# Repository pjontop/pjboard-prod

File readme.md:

# PJBOARD!!!

PJBoard is a low-profile, wireless split keyboard with 42 keys, two displays, and a very very thin case!

I made this because I wanted something that had the clean look of keyboards like the Geist Totem and the portability of the Voyager, but with a few more keys so it would be easier for me to actually learn how to use a split keyboard. Basically: how close can I get to the MacBook Pro of keyboards?

It uses Kailh Choc switches, two SuperMini nRF52840 controllers, nice!view displays, and ZMK firmware. Each half is completely wireless and has its own battery, power switch, and reset button.

## Features

- 42-key split layout: 3 rows of 6 keys and 3 thumb keys on each side
- Low-profile Kailh Choc switches
- Hotswap sockets, because desoldering an entire keyboard would not be very fun
- Fully wireless using two SuperMini nRF52840 controllers
- A nice!view display on each half for status info
- A super thin, rounded case with hidden screws
- Separate base, plate, and display-cover pieces for each half
- Power and reset switches built directly into both PCBs
- Three ZMK layers: Base, Lower, and Raise

## CAD Model

The case was made in Onshape. I started by importing the PCB outline and building everything around it, which sounds simple until Onshape decides one switch model needs approximately one billion triangles and takes four hours to import :sob:

The final case is made from three parts per side: the base, the switch plate, and the display cover. I wanted it to be really thin, rounded, and clean, so the mounting hardware is hidden and the top pieces sit flush with the case. There are also cutouts underneath the larger components so the case does not need to be unnecessarily chonky.

You can view and remix the original CAD here: **[PJBoard on Onshape](https://cad.onshape.com/documents/bca79db99613f7f3e83bd048/w/cf08fbd1a130c559ac00717d/e/9940d6e044f49ffd99b80cc9?renderMode=0&uiState=6a8a41c1502d0c8b6353df97)**

## PCB

Here is the PCB! It was designed in KiCad and it was definitely the largest rabbit hole in this entire project.

Each half uses a 4x6 key matrix with 21 populated positions, one diode per key, a SuperMini nRF52840, a nice!view header, an on/off switch, and a reset button. I moved the diodes into the centre control area to keep the switch area clean and used both copper layers to make the matrix routing actually possible.

The two halves are panelized together with breakaway tabs, so they can be manufactured as one PCB and snapped apart afterward. Fire, right?

## Firmware Overview

PJBoard runs [ZMK](https://zmk.dev/) since the keyboard is wireless. Prebuilt firmware for both halves is included in the [`firmware`](firmware/) folder, along with the source configuration.

The current keymap has three layers:

- **Base:** the normal QWERTY layout
- **Lower:** numbers, arrow keys, and Bluetooth controls
- **Raise:** symbols and brackets

The two thumb layer keys make it possible to keep the board at only 42 keys without losing all the useful stuff. The displays stay visible while the keyboard is awake and show the current keyboard status.

## BOM

Here should be the main stuff you need to build PJBoard:

A better BOM Can be found in the bom.csv in the main directory, this is merely meant for a rough look over.

- 42x Kailh Choc low-profile switches
- 42x Kailh Choc hotswap sockets
- 42x low-profile keycaps
- 42x SOD-123 diodes
- 2x SuperMini nRF52840 controllers
- 2x nice!view displays
- 2x small LiPo batteries
- 2x SMD power switches
- 2x SMD reset buttons
- 1x left/right PCB set
- 1x printed case set (left and right base, plate, and display cover)
- M2 hardware for mounting the PCBs and case parts

## Things I Learnt

This was my first time going this deep into designing a keyboard, and I learnt a TON.

- How keyboard matrices actually work instead of just vaguely knowing that diodes exist
- How to make and edit custom KiCad symbols and footprints
- How to route a two-layer split keyboard PCB without creating a heavenly amount of vias
- How to use multi-channel design tools instead of manually mirroring everything for 40 minutes
- How to bring a PCB outline into Onshape and design a case around the real dimensions
- How much the angle, stagger, and thumb position matter when designing for actual hands
- How ZMK separates boards, shields, keymaps, and configuration files (the naming absolutely did not help at first)
- That testing a layout before committing to the PCB saves a LOT of pain later

## Challenges I Faced

KiCad was the main villain here. I redesigned the PCB more than once, moved all the diodes around, fought with mirrored layouts, installed a plugin that did not even do what I needed, and eventually figured out a routing setup that was way cleaner. Sad reality: sometimes you really do just have to reroute the entire board.

The case also took a bunch of iteration. I wanted it thin, rounded, strong around the high-pressure keys, and completely clean from the top with no visible screws. Getting all of those things at once was much harder than sketching them, especially while keeping enough room for the hotswap sockets, batteries, controllers, and displays.

The firmware was another whole thing. ZMK is really powerful, but understanding boards vs shields, setting up both halves, fixing the matrix, and getting the displays working was WAY worse than I thought it would be. YouTube tutorials, random websites, and an unreasonable amount of debugging carried me through it.

Overall, though, I am super happy with how it turned out. I went from a rough idea and a hand sketch to a complete PCB, case, and working firmware setup. Very very fire.

## Thank You!

I am super thankful to [Hack Club](https://hackclub.com/) for funding this project and making it possible for me to actually build the weird keyboard I spent way too many hours obsessing over.

Also, Macondo is awesome. Seriously. Programs like this are the reason I can learn hardware by actually making something real instead of just watching another tutorial and forgetting everything five minutes later.

alr toodles :3

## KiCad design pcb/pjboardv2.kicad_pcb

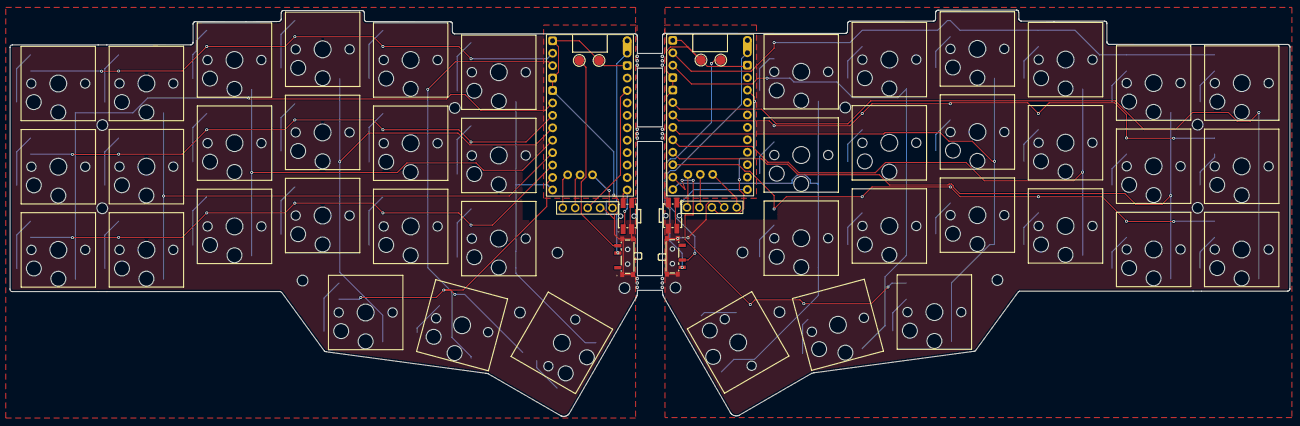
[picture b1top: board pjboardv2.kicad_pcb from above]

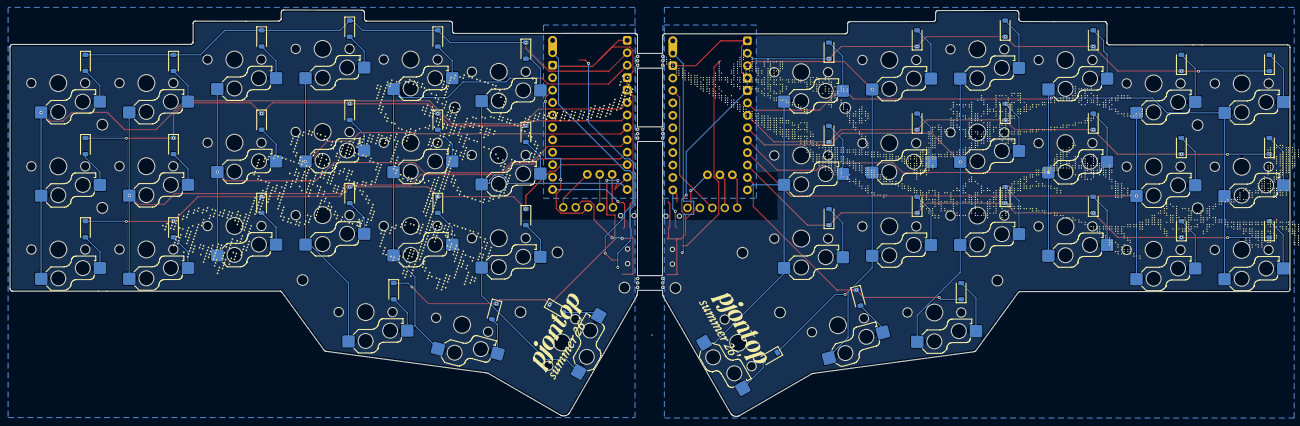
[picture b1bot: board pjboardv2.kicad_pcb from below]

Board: 2 copper layers, 261.5 x 83.0 mm, 113 parts (49 on the bottom side), 77 nets.

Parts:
D1, D2, D3, D4, D5, D6, D7, D8, D9, D10, D11, D12, D13, D14, D15, D16, D17, D18, D19, D20, D21, D22, D23, D24, D25, D26, D27, D28, D29, D30, D31, D32, D33, D34, D35, D36, D37, D38, D39, D40, D41, D42: D; D_SOD-123
Display3, Display4: nice!view; nice_view
H1, H2, H3: MountingHole; BreakawayTab
H4, H5, H6, H7, H8, H9, H10, H11, H12, H13, H14, H15, H16, H17: MountingHole; MountingHole_M2_NPTH
SW1, SW2, SW3, SW4, SW5, SW6, SW7, SW8, SW9, SW10, SW11, SW12, SW13, SW14, SW15, SW16, SW17, SW18, SW19, SW20, SW21, SW24, SW25, SW26, SW27, SW28, SW29, SW30, SW31, SW32, SW33, SW34, SW35, SW36, SW37, SW38, SW39, SW40, SW41, SW42, SW43, SW44: SW_Push; SW_Hotswap_Kailh_Choc_V1_Assembly
SW47, SW48: SSSS811101; SW-SMD_SSSS811101
SW49, SW50: TS-1114S-26; SW-SMD_4P-L4.7-W4.5-P1.70-LS6.4-EH
TP1, TP2, TP3, TP4: TestPoint; TestPoint_Pad_D2.0mm
U5, U6: SuperMini nRF52840; SuperMini_nRF52840_AH_USBup

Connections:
/left/COL0: SW1.1, SW2.1, SW3.1, U5.5 (P0.17)
/left/COL1: SW4.1, SW5.1, SW6.1, U5.9 (P1.00)
/left/COL2: SW7.1, SW8.1, SW9.1, U5.8 (P0.24)
/left/COL3: SW10.1, SW11.1, SW12.1, SW13.1, U5.7 (P0.22)
/left/COL4: SW14.1, SW15.1, SW16.1, SW17.1, U5.2 (P0.08)
/left/COL5: SW18.1, SW19.1, SW20.1, SW21.1, U5.12 (P1.06-LF)
/left/NVCC: Display3.3 (VCC), U5.16 (3V3)
/left/NVCS: Display3.5 (CS), U5.27 (P1.07-LF)
/left/NVMOSI: Display3.1 (MOSI), U5.25 (P1.01-LF)
/left/NVSCK: Display3.2 (SCK), U5.26 (P1.02-LF)
/left/ROW0: D1.1 (K), D4.1 (K), D7.1 (K), D10.1 (K), D14.1 (K), D18.1 (K), U5.1 (P0.06)
/left/ROW1: D2.1 (K), D5.1 (K), D8.1 (K), D11.1 (K), D15.1 (K), D19.1 (K), U5.6 (P0.20)
/left/ROW2: D3.1 (K), D6.1 (K), D9.1 (K), D12.1 (K), D16.1 (K), D20.1 (K), U5.10 (P0.11)
/left/ROW3: D13.1 (K), D17.1 (K), D21.1 (K), U5.11 (P1.04-LF)
/left/SRST: SW49.1, SW49.2, U5.24 (P0.09-LF)
/left/SWBAT+: SW47.2, U5.13 (BAT+), U5.29 (BAT+)
/right/COL0: SW24.1, SW25.1, SW26.1, U6.5 (P0.17)
/right/COL1: SW27.1, SW28.1, SW29.1, U6.9 (P1.00)
/right/COL2: SW30.1, SW31.1, SW32.1, U6.8 (P0.24)
/right/COL3: SW33.1, SW34.1, SW35.1, SW36.1, U6.7 (P0.22)
/right/COL4: SW37.1, SW38.1, SW39.1, SW40.1, U6.2 (P0.08)
/right/COL5: SW41.1, SW42.1, SW43.1, SW44.1, U6.12 (P1.06-LF)
/right/NVCC: Display4.3 (VCC), U6.16 (3V3)
/right/NVCS: Display4.5 (CS), U6.27 (P1.07-LF)
/right/NVMOSI: Display4.1 (MOSI), U6.25 (P1.01-LF)
/right/NVSCK: Display4.2 (SCK), U6.26 (P1.02-LF)
/right/ROW0: D22.1 (K), D25.1 (K), D28.1 (K), D31.1 (K), D35.1 (K), D39.1 (K), U6.1 (P0.06)
/right/ROW1: D23.1 (K), D26.1 (K), D29.1 (K), D32.1 (K), D36.1 (K), D40.1 (K), U6.6 (P0.20)
/right/ROW2: D24.1 (K), D27.1 (K), D30.1 (K), D33.1 (K), D37.1 (K), D41.1 (K), U6.10 (P0.11)
/right/ROW3: D34.1 (K), D38.1 (K), D42.1 (K), U6.11 (P1.04-LF)
/right/SRST: SW50.1, SW50.2, U6.24 (P0.09-LF)
/right/SWBAT+: SW48.2, U6.13 (BAT+), U6.29 (BAT+)
GND: Display3.4 (GND), Display4.4 (GND), SW47.4, SW47.5, SW47.6, SW47.7, SW48.4, SW48.5, SW48.6, SW48.7, SW49.3, SW49.4, SW50.3, SW50.4, TP2.1 (1_1), TP4.1 (1_1), U5.3 (GND), U5.4 (GND), U5.14 (GND), U5.28 (GND), U6.3 (GND), U6.4 (GND), U6.14 (GND), U6.28 (GND)
unnamed: D1.2 (A), SW1.2
unnamed: D2.2 (A), SW2.2
unnamed: D3.2 (A), SW3.2
unnamed: D4.2 (A), SW4.2
unnamed: D5.2 (A), SW5.2
unnamed: D6.2 (A), SW6.2
unnamed: D7.2 (A), SW7.2
unnamed: D8.2 (A), SW8.2
unnamed: D9.2 (A), SW9.2
unnamed: D10.2 (A), SW10.2
unnamed: D11.2 (A), SW11.2
unnamed: D12.2 (A), SW12.2
unnamed: D13.2 (A), SW13.2
unnamed: D14.2 (A), SW14.2
unnamed: D15.2 (A), SW15.2
unnamed: D16.2 (A), SW16.2
unnamed: D17.2 (A), SW17.2
unnamed: D18.2 (A), SW18.2
unnamed: D19.2 (A), SW19.2
unnamed: D20.2 (A), SW20.2
unnamed: D21.2 (A), SW21.2
unnamed: D22.2 (A), SW24.2
unnamed: D23.2 (A), SW25.2
unnamed: D24.2 (A), SW26.2
unnamed: D25.2 (A), SW27.2
unnamed: D26.2 (A), SW28.2
unnamed: D27.2 (A), SW29.2
unnamed: D28.2 (A), SW30.2
unnamed: D29.2 (A), SW31.2
unnamed: D30.2 (A), SW32.2
unnamed: D31.2 (A), SW33.2
unnamed: D32.2 (A), SW34.2
unnamed: D33.2 (A), SW35.2
unnamed: D34.2 (A), SW36.2
unnamed: D35.2 (A), SW37.2
unnamed: D36.2 (A), SW38.2
unnamed: D37.2 (A), SW39.2
unnamed: D38.2 (A), SW40.2
unnamed: D39.2 (A), SW41.2
unnamed: D40.2 (A), SW42.2
unnamed: D41.2 (A), SW43.2
unnamed: D42.2 (A), SW44.2
unnamed: SW47.3, TP1.1 (1_1)
unnamed: SW48.3, TP3.1 (1_1)
